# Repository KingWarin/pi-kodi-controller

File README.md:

# pi-kodi-controller
Fiddling aroung with the pi, kodi and a breadboard

Note:  
    Additionaly the xbmcclient script is needed.  
    This can be found in the [XBMC Repository](https://github.com/xbmc/xbmc)  
    at [xbmcclient](https://github.com/xbmc/xbmc/blob/master/tools/EventClients/lib/python/xbmcclient.py)

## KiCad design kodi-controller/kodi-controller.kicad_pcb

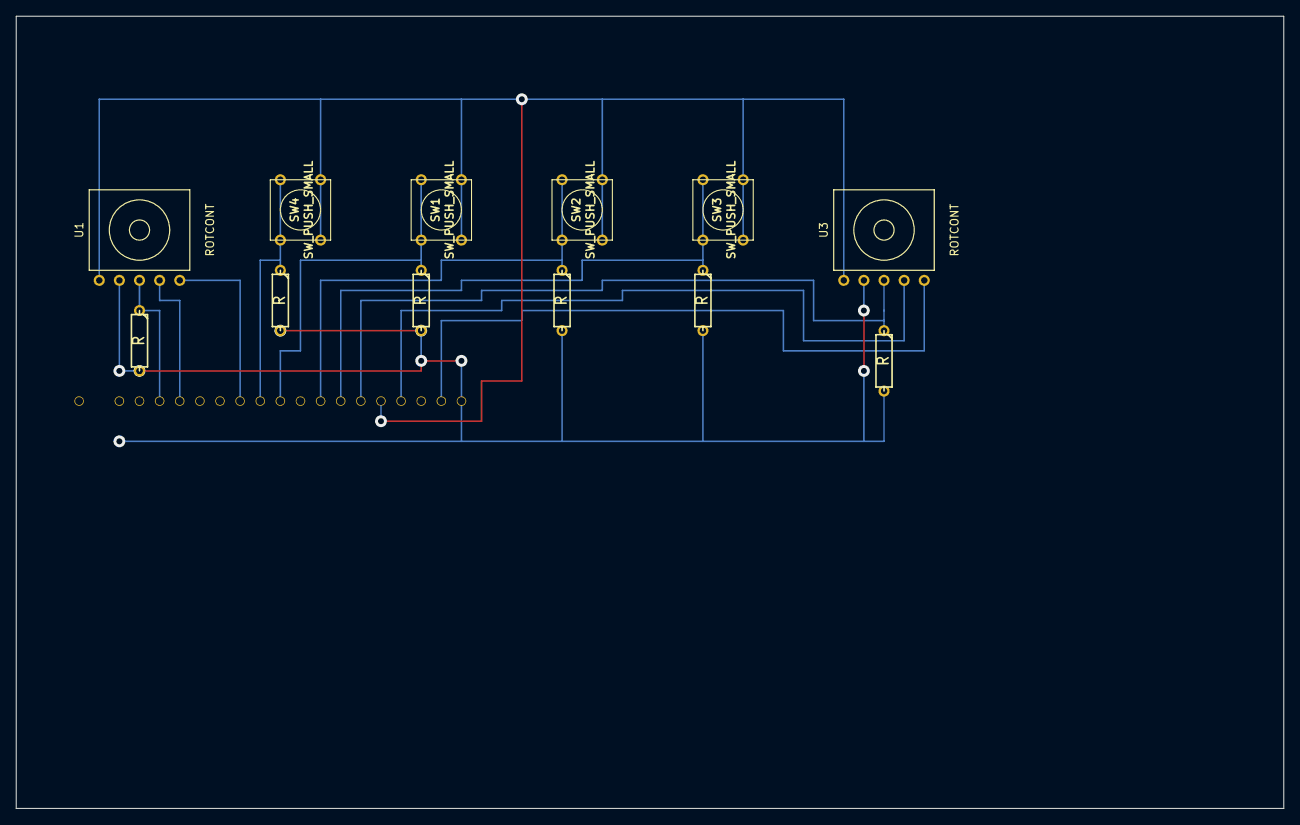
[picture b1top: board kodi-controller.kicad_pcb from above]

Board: 2 copper layers, 160.0 x 100.0 mm, 13 parts (1 on the bottom side), 12 nets.

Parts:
R1, R2, R3, R4, R5, R6: R; R3
SW1, SW2, SW3, SW4: SW_PUSH_SMALL
U1, U3: ROTCONT; rotaryController
U2: PINS; pins

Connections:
+3.3V: R1.2, R2.2, R3.2, R4.2, R5.2, R6.2, U1.2, U2.20, U3.2
GND: SW1.2, SW2.2, SW3.2, SW4.2, U1.1, U2.16, U3.1
unnamed: U2.17, U3.4
unnamed: U2.19, U3.5
unnamed: U1.4, U2.6
unnamed: R1.1, U1.3, U2.5
unnamed: U1.5, U2.9
unnamed: R2.1, SW1.1, U2.11
unnamed: R3.1, SW2.1, U2.13
unnamed: R4.1, SW3.1, U2.14
unnamed: R5.1, SW4.1, U2.10
unnamed: R6.1, U2.15, U3.3

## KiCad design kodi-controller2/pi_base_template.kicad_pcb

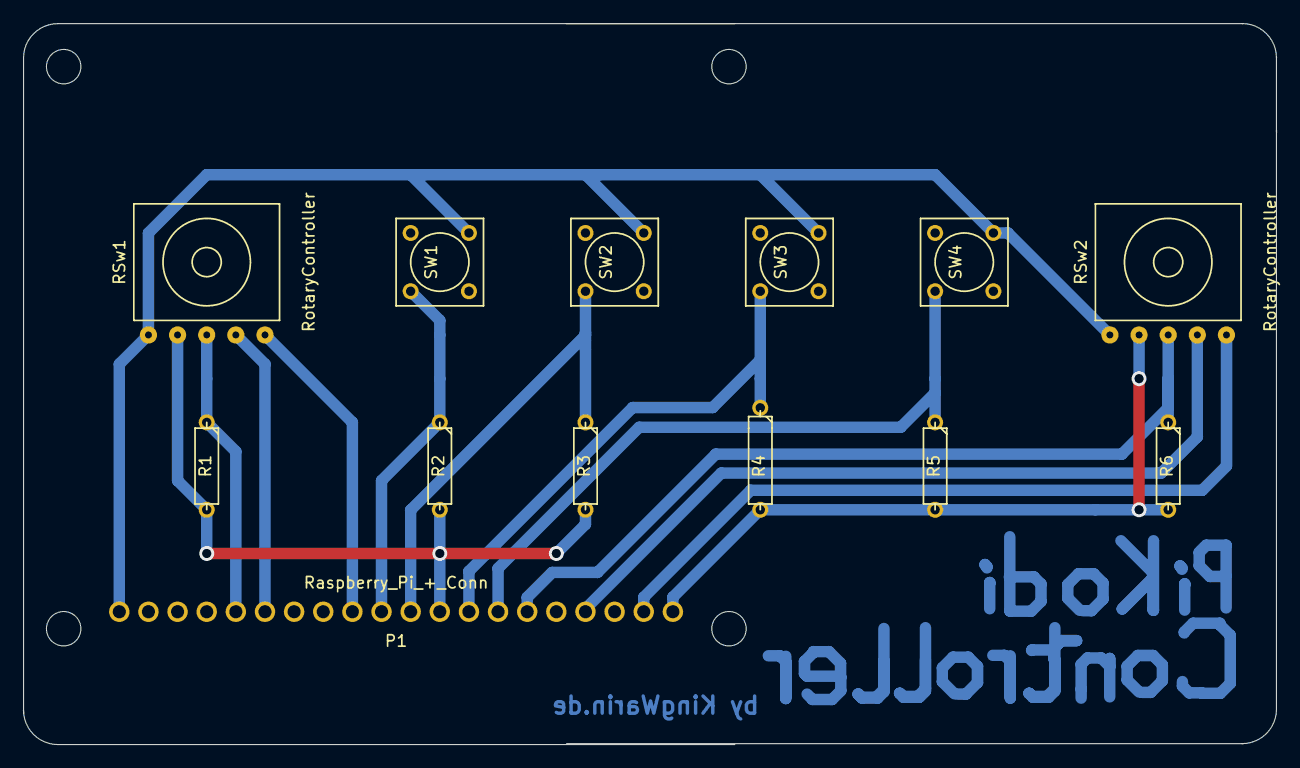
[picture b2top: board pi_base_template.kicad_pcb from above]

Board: 2 copper layers, 109.2 x 62.9 mm, 13 parts (0 on the bottom side), 12 nets.

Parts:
P1: Raspberry_Pi_+_Conn; pins
R1, R2, R3, R4, R5, R6: R; R3
RSw1, RSw2: RotaryController; rotaryController
SW1, SW2, SW3, SW4: SW_PUSH_SMALL

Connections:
+3V3: P1.1, P1.9, R1.2, R2.2, R3.2, R4.2, R5.2, R6.2, RSw1.2, RSw2.2
GND: P1.5, P1.13, P1.20, RSw1.1, RSw2.1, SW1.2, SW2.2, SW3.2, SW4.2
unnamed: P1.2, RSw2.5
unnamed: P1.4, RSw2.4
unnamed: P1.6, R6.1, RSw2.3
unnamed: P1.7, R5.1, SW4.1
unnamed: P1.8, R4.1, SW3.1
unnamed: P1.10, R3.1, SW2.1
unnamed: P1.11, R2.1, SW1.1
unnamed: P1.12, RSw1.5
unnamed: P1.15, RSw1.4
unnamed: P1.16, R1.1, RSw1.3

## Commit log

2016-07-23 Added gitignore.
2016-07-23 Add already existing files.
2016-07-23 Add single-switch for buttons and comments.
2016-07-23 Remove old code.
2016-07-23 Add link to the xbmc repository.
2016-07-23 README styling.
2016-07-25 Code cleanup and new rotaryEncoder.
2016-07-25 Switch rotaryController pins / switch direction.
2016-08-05 Added new functions and buttons.
    Well, just added new functions for play/pause, one level back, prev/next
    item and the according buttons to the setup.
    Also adapted the pins for the to-be-produced board for the workshop
    mediacenter.
2016-08-07 Add KiCAD Files for board
2016-08-10 Add new kodi-controller kicad files.
2016-08-11 Finished new board layout
2016-08-13 KodeController2: Switched footprint pin positions for push switches.
2016-08-17 Updated clearances.
2016-08-18 Filled the board once more.
2016-08-18 Update page settings.
2016-08-20 Adapt pin numbers to meet board layout.
2016-08-21 Switched pins for rotaryEncoders to match direction.
2016-08-22 Removed old circuit board files.

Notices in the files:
kodi-controller2/pi_base_template.kicad_pcb:
License: CERN OHL V1.2
